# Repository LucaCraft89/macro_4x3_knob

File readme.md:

# macro_4x3_knob

Image Coming soon

* Keyboard Creators: 
- [Luca Dall'Acqua](https://github.com/lucacraft89) PCB and FW
- [Simone Folino](https://github.com/Simone02472) 3D Modeling
* Hardware Supported: Arduino Pro Micro, Custom PCB
* Hardware Availability: AliExpress or any mayor online store
* Status: New improved PCB revision and subsequent 3d Model revision in development

Make example for this keyboard (after setting up your build environment):
```bash
make macro_4x3_knob:default
```
Flashing example for this keyboard:
```bash
make macro_4x3_knob:default:flash
```
See the [build environment setup](https://docs.qmk.fm/#/getting_started_build_tools) and the [make instructions](https://docs.qmk.fm/#/getting_started_make_guide) for more information. Brand new to QMK? Start with our [Complete Newbs Guide](https://docs.qmk.fm/#/newbs).

## 3D models 
| Part  | File |
| :---     |    :----:   | 
| TOP      | [V1.0](https://github.com/LucaCraft89/macro_4x3_knob/3D/V1/top1.0.STL)      | 
| BOTTOM   | [V1.0](https://github.com/LucaCraft89/macro_4x3_knob/3D/V1/bottom1.0.STL)      | 

## Gerber files

[V1](https://github.com/LucaCraft89/macro_4x3_knob/PCB/Gerber/V1/V1.zip)
- NOTE: PCB has space for oled display that was never implemented, ignore it

## VIAL
VIAL is supported just flash the layout
```bash
make macro_4x3_knob:vial:flash
```

## Bootloader
Enter the bootloader in 3 ways:

* **Bootmagic reset**: Hold down the key at (0,0) in the matrix (usually the top left key or Escape) and plug in the keyboard
* **Physical reset button**: Briefly press the button on the back of the PCB - some may have pads you must short instead
* **Keycode in layout**: Press the key mapped to `QK_BOOT` if it is available

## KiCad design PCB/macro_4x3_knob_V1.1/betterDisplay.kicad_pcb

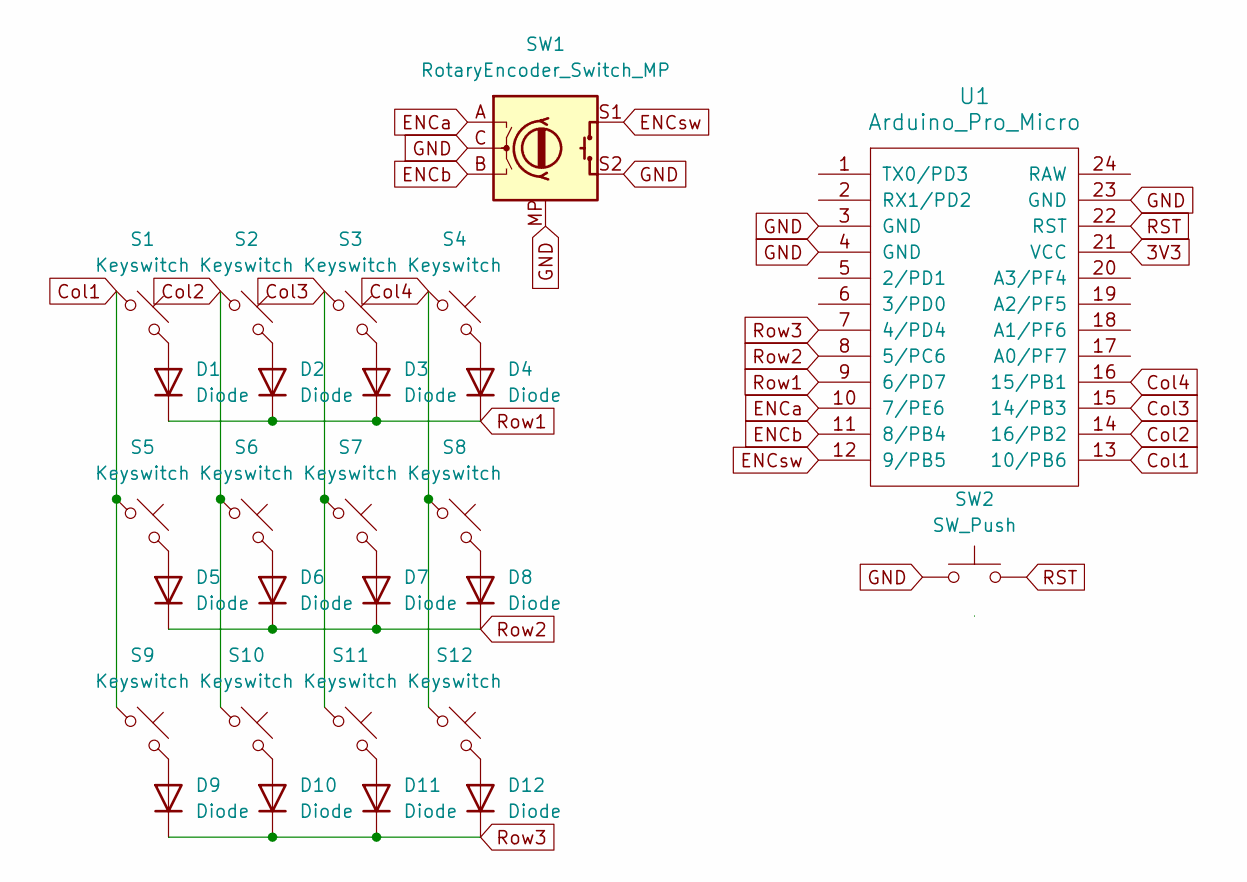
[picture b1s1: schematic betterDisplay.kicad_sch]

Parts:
D1, D2, D3, D4, D5, D6, D7, D8, D9, D10, D11, D12: Diode; Diode_DO-35
S1, S2, S3, S4, S5, S6, S7, S8, S9, S10, S11, S12: Keyswitch; MX_PCB_1.00u
SW1: RotaryEncoder_Switch_MP; Encoder_EC11_MX
SW2: SW_Push; SW_PUSH_6mm
U1: Arduino_Pro_Micro

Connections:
3V3: U1.21 (VCC)
Col1: S1.1, S5.1, S9.1, U1.13 (10/PB6)
Col2: S2.1, S6.1, S10.1, U1.14 (16/PB2)
Col3: S3.1, S7.1, S11.1, U1.15 (14/PB3)
Col4: S4.1, S8.1, S12.1, U1.16 (15/PB1)
ENCa: SW1.A, U1.10 (7/PE6)
ENCb: SW1.B, U1.11 (8/PB4)
ENCsw: SW1.S1, U1.12 (9/PB5)
GND: SW1.C, SW1.MP, SW1.S2, SW2.1, U1.3 (GND), U1.4 (GND), U1.23 (GND); also elsewhere on the board
unnamed: D1.2 (A), S1.2
unnamed: D2.2 (A), S2.2
unnamed: D3.2 (A), S3.2
unnamed: D4.2 (A), S4.2
unnamed: D5.2 (A), S5.2
unnamed: D6.2 (A), S6.2
unnamed: D7.2 (A), S7.2
unnamed: D8.2 (A), S8.2
unnamed: D9.2 (A), S9.2
unnamed: D10.2 (A), S10.2
unnamed: D11.2 (A), S11.2
unnamed: D12.2 (A), S12.2
RST: SW2.2, U1.22 (RST)
Row1: D1.1 (K), D2.1 (K), D3.1 (K), D4.1 (K), U1.9 (6/PD7)
Row2: D5.1 (K), D6.1 (K), D7.1 (K), D8.1 (K), U1.8 (5/PC6)
Row3: D9.1 (K), D10.1 (K), D11.1 (K), D12.1 (K), U1.7 (4/PD4)

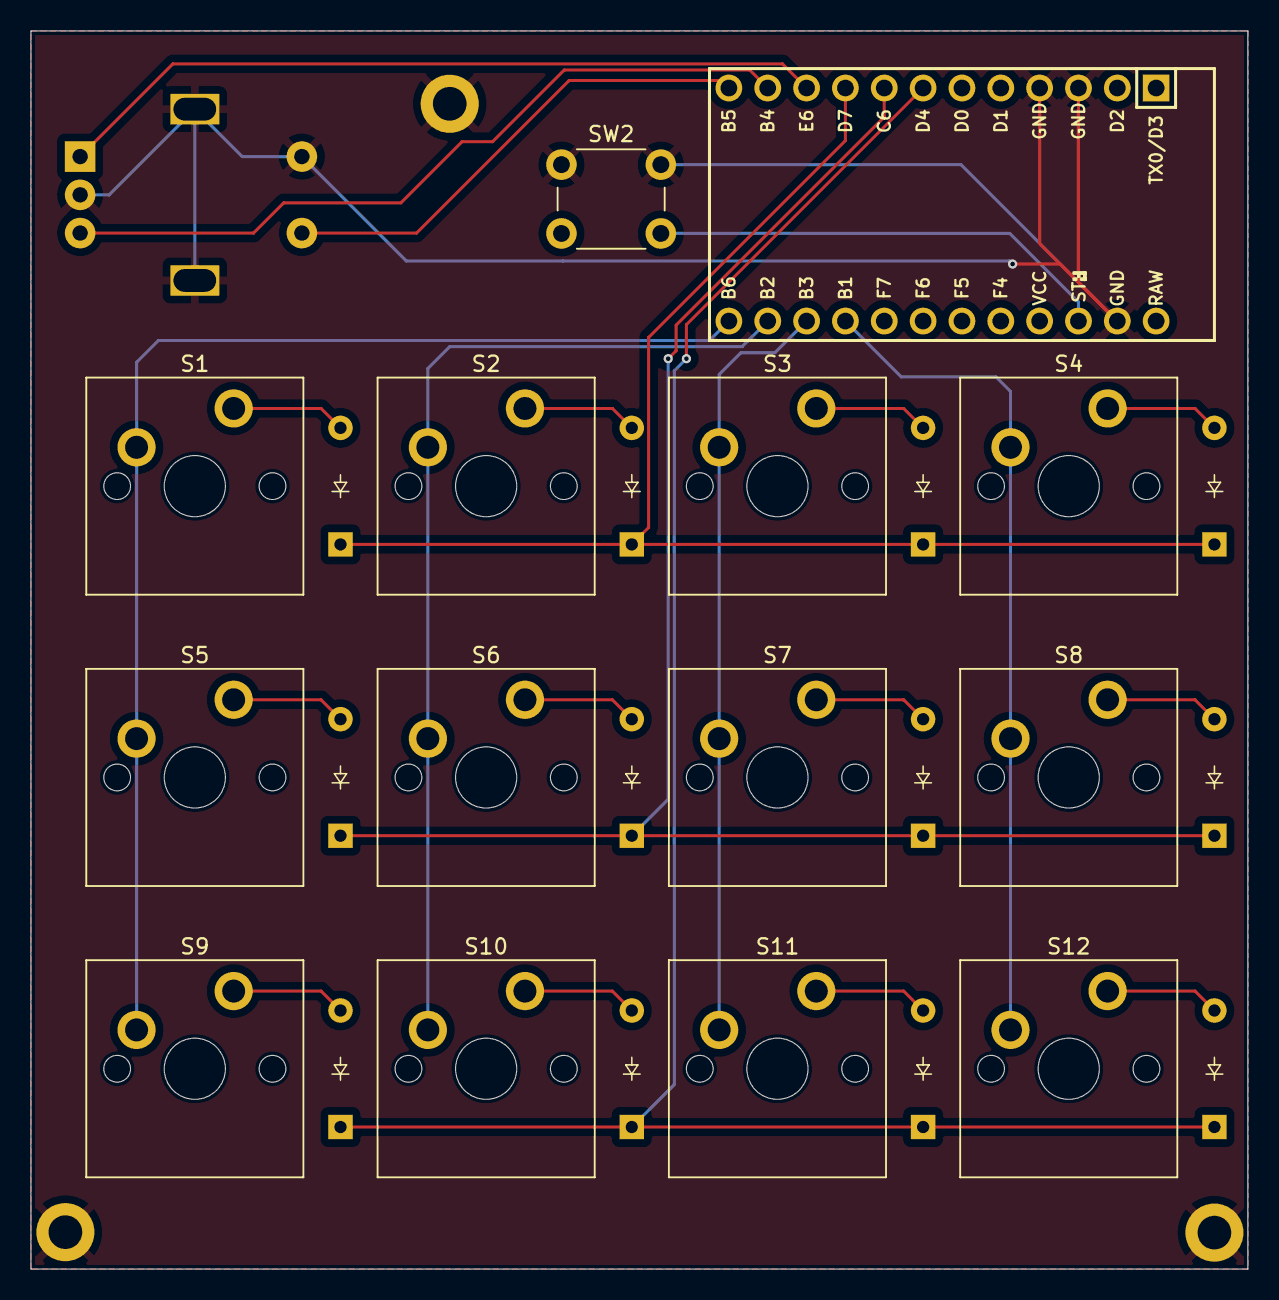
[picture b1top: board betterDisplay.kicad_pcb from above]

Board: 2 copper layers, 79.6 x 81.0 mm, 28 parts (0 on the bottom side), 24 nets.

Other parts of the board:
GND: MountingHole_2.2mm_M2_ISO14580_Pad

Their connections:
GND: GND.1; also elsewhere on the board

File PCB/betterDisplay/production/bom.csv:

Designator,Footprint,Quantity,Value,LCSC Part #
"D1, D10, D11, D12, D2, D3, D4, D5, D6, D7, D8, D9",Diode_DO-35,12,Diode,
J1,OLED_128x32,1,OLED_128x32,
"S1, S10, S11, S12, S2, S3, S4, S5, S6, S7, S8, S9",MX_PCB_1.00u,12,Keyswitch,
SW1,Encoder_EC11_MX,1,RotaryEncoder_Switch_MP,
U1,Arduino_Pro_Micro,1,Arduino_Pro_Micro,

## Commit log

2025-05-29 Initial
2025-05-29 Fix Readme
2025-05-29 Add 3d
2025-05-30 Added New PCB
2025-05-30 Fixed file Names
